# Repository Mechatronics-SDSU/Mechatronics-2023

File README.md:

# SDSU Mechatronics 2023

# About contributions

If you are unsure where to start, ask Software Project Manager or Software Lead.

Build and environment setup instructions are located in the docs. Refer to them before running `git clone` on this repository!

# About this repo

This repository has required code styling and commit rules. See style guide below for details.

ONLY upload source code. Do NOT commit binaries or Docker containers to this repository.

Pull request to master requirements:
Approved PR in `yourfeaturename-beta` branch from ANY project manager or the software lead is *required*. See below for details.

To begin development on a new feature, it is *recommended* to create a new branch from the `beta` branch, not the `master` branch, naming it `yourfeaturename_yourfulltable-dev`. When code is ready for submission, code is *required* be merged to a `yourfeaturename-beta` branch where a PR is then submitted, along with linking relevant issues here on GitHub. ***If you do NOT name your branch with the*** `-beta` ***naming convention, it is assumed the code is not ready to be merged and as a result will not be merged***.

Contributions are tracked via Git and GitHub but it is still *recommended* to comment your name and date on files worked on.

[Python installation and setup guide](src/man/python_setup_guide.md)

Python styling guide: All code in Python must follow [our styling guide](src/man/styling_guide.md).

C/C++ styling guide: All C/C++ code must follow the [Linux Kernal styling guide](https://www.kernel.org/doc/html/v4.10/process/coding-style.html).

Git naming conventions and usage: To make your own branches and push to this repository, read [our Git Guide](src/man/git_guide.md).

# About Scion

### Scion is the SDSU Mechatronics robot for the 2022 RoboSub Competition.

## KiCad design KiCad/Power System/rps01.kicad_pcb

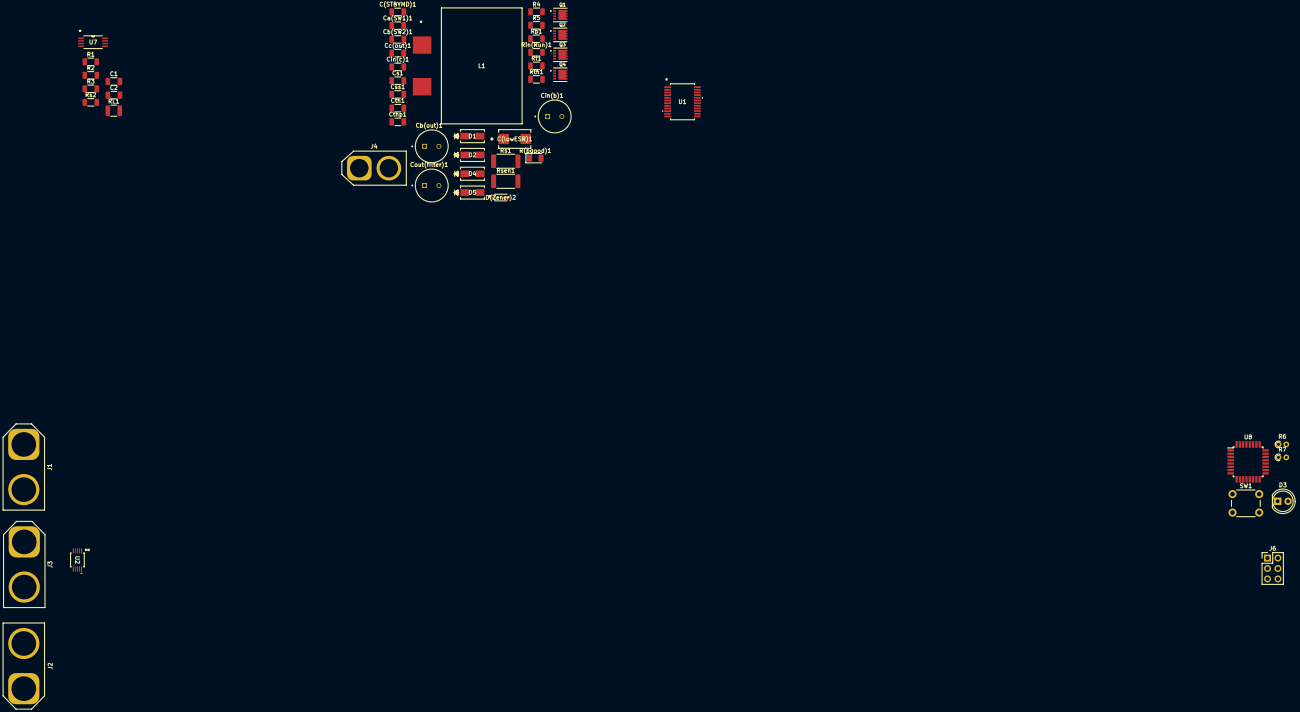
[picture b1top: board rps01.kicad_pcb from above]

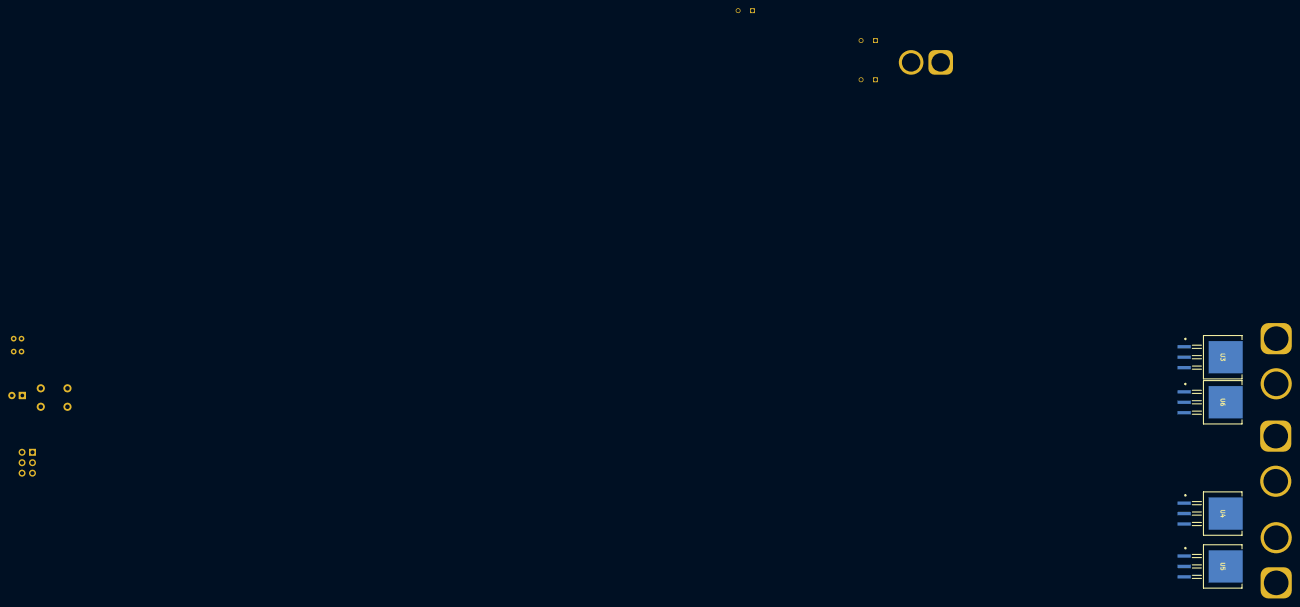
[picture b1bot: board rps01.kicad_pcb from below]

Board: 2 copper layers, 56 parts (4 on the bottom side), 38 nets, no tracks yet.

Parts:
C1, C2: 0.1mu; C_1206_3216Metric
C(STBYMD)1: 0.001u; C_1206_3216Metric
C(lowESR)1: 4.7u; LOWESRCAPMP7.6X4.3_3.1N_KEM
Ca(SW1)1: 0.22u; C_1206_3216Metric
Cb(SW2)1: 0.22u; C_1206_3216Metric
Cb(out)1: 330u; LargeCAPSCAPPRD350W60D800H1200
Cc(out)1: 47u; C_1206_3216Metric
Cin(b)1: 270u; LargeCAPSCAPPRD350W60D800H1200
Cin(c)1: 10u; C_1206_3216Metric
Cout(filter)1: 330u; LargeCAPSCAPPRD350W60D800H1200
Cs1: 100p; C_1206_3216Metric
Css1: 0.001u; C_1206_3216Metric
Cth1: 10000p; C_1206_3216Metric
Cthp1: 47p; C_1206_3216Metric
D1, D2, D4, D5: D_Schottky; CR_SMA_320-340AE_DIO
D3: LED; LED_D5.0mm
D(Zener)2: D_Zener; SOD123_DIO
J1: XT90 BAT1; AMASS_XT90-F_1x02_P11.00mm_Vertical
J2: XT90 BAT2; AMASS_XT90-F_1x02_P11.00mm_Vertical
J3: XT90 ESC Output; AMASS_XT90-M_1x02_P11.00mm_Vertical
J4: XT30PW Horizontal; AMASS_XT60-F_1x02_P7.20mm_Vertical
J6: 6pin; PinHeader_2x03_P2.54mm_Vertical
L1: 6.8u; IND_410680_WRE
Q1, Q2, Q3, Q4: NMOS; Q1Q2TRANS_FDMC86520L
R1: 4.7k; R_1206_3216Metric
R2: 10k; R_1206_3216Metric
R3: 1k; R_1206_3216Metric
R4, R5: 100; R_1206_3216Metric
R6: 10K; R_Axial_DIN0204_L3.6mm_D1.6mm_P1.90mm_Vertical
R7: 1k; R_Axial_DIN0204_L3.6mm_D1.6mm_P1.90mm_Vertical
R(pgood)1: 100k; LED_1206_3216Metric
RL1: 72.3k; R_1210_3225Metric
Rb1: 4.3K; R_1206_3216Metric
Rin(Run)1: 51K; R_1206_3216Metric
Rs1: 6m; R_2512_6332Metric
Rs2: 0.5m; R_1206_3216Metric
Rsen1: 6m; R_2512_6332Metric
Rt1: 100K; R_1206_3216Metric
Rth1: 124K; R_1206_3216Metric
SW1: SW_Push_Open; SW_PUSH_6mm
U1: LTC3780EG-TRPBF; SSOP-24_G_LIT
U2: LTC4416EMS-1-TRPBF; MSOP-10_MS_LIT
U3, U4, U5, U6: NP100P04PLG-E1-AY; PRSS0004AL-A_REN
U7: INA139NA/250; PW8
U8: ATmega328PB-A; TQFP-32_7x7mm_P0.8mm

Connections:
+5V: J6.5, R6.2, U8.4 (VCC)
/19V Boost/Vout: Cb(out)1.1, Cc(out)1.1, Cout(filter)1.1, D1.1 (K), J4.1, Q3.1 (D), Rt1.1
/Load Sharing/G1: U2.10 (G1), U3.1 (GATE), U6.1 (GATE)
/Load Sharing/G2: U2.6 (G2), U4.1 (GATE), U5.1 (GATE)
/Load Sharing/V1: J1.2, U2.2 (E1), U2.9 (V1), U3.2 (DRAIN), U3.4 (FIN), U6.2 (DRAIN), U6.4 (FIN)
/Load Sharing/V2: J2.2, U2.7 (V2), U4.2 (DRAIN), U4.4 (FIN), U5.2 (DRAIN), U5.4 (FIN)
/Load Sharing/VS: Cin(b)1.1, Cin(c)1.1, J3.1, Q1.1 (D), Rin(Run)1.1, U1.21 (VIN), U2.8 (VS), U3.3 (SOURCE), U4.3 (SOURCE), U5.3 (SOURCE), U6.3 (SOURCE)
GND: C1.2, C2.1, C(STBYMD)1.2, C(lowESR)1.2, Cb(out)1.2, Cc(out)1.2, Cin(b)1.2, Cin(c)1.2, Cout(filter)1.2, Css1.1, Cth1.2, Cthp1.2, D(Zener)2.2 (A), J1.1, J2.1, J3.2, J4.2, J6.1, R3.2, R5.2, R7.2, RL1.2, Rb1.2, Rs1.2, Rsen1.2, SW1.1 (A), U1.7 (SGND), U1.9 (FCB), U1.10 (PLLFLTR), U1.17 (PGND), U1.20 (EXTVCC), U2.3 (GND), U2.4 (*E2), U7.2 (GND), U8.5 (GND), U8.21 (GND)
MISO: J6.6, U8.16 (PB4)
MOSI: J6.3, U8.15 (PB3)
unnamed: C1.1, R2.2, R3.1
unnamed: Cth1.1, Rth1.1
unnamed: Ca(SW1)1.2, D1.2 (A), L1.2, Q3.3 (S), Q4.1 (D), U1.22 (SW1)
unnamed: D2.2 (A), Q2.3 (S), Q4.3 (S), R4.1, Rs1.1, Rsen1.1
unnamed: Cb(SW2)1.1, D2.1 (K), L1.1, Q1.3 (S), Q2.1 (D), U1.15 (SW2)
unnamed: D3.2 (A), U8.13 (PB1)
unnamed: D3.1 (K), R7.1
unnamed: C(lowESR)1.1, D4.2 (A), D5.2 (A), R(pgood)1.1, U1.19 (INTVCC)
unnamed: Ca(SW1)1.1, D4.1 (K), U1.24 (BOOST1)
unnamed: Cb(SW2)1.2, D5.1 (K), U1.13 (BOOST2)
unnamed: D(Zener)2.1 (K), Rin(Run)1.2, U1.8 (RUN)
unnamed: J6.2, R6.1, SW1.2 (B), U8.29 (~RESET/PC6)
unnamed: Q1.2 (G), U1.14 (TG2)
unnamed: Q2.2 (G), U1.16 (BG2)
unnamed: Q3.2 (G), U1.23 (TG1)
unnamed: Q4.2 (G), U1.18 (BG1)
unnamed: R1.2, R2.1
unnamed: Cthp1.1, Rth1.2, U1.5 (ITH)
unnamed: R(pgood)1.2, U1.1 (PGOOD)
unnamed: Cs1.2, R4.2, U1.3 (SENSE+)
unnamed: Cs1.1, R5.1, U1.4 (SENSE-)
unnamed: Css1.2, U1.2 (SS)
unnamed: C(STBYMD)1.1, U1.12 (STBYMD)
unnamed: Rb1.1, Rt1.2, U1.6 (VOSENSE)
unnamed: C2.2, RL1.1, U7.1 (OUT)
unnamed: R1.1, Rs2.1, U7.3 (VIN+), U7.5 (V+)
unnamed: Rs2.2, U7.4 (VIN-)
SCK: J6.4, U8.17 (PB5)

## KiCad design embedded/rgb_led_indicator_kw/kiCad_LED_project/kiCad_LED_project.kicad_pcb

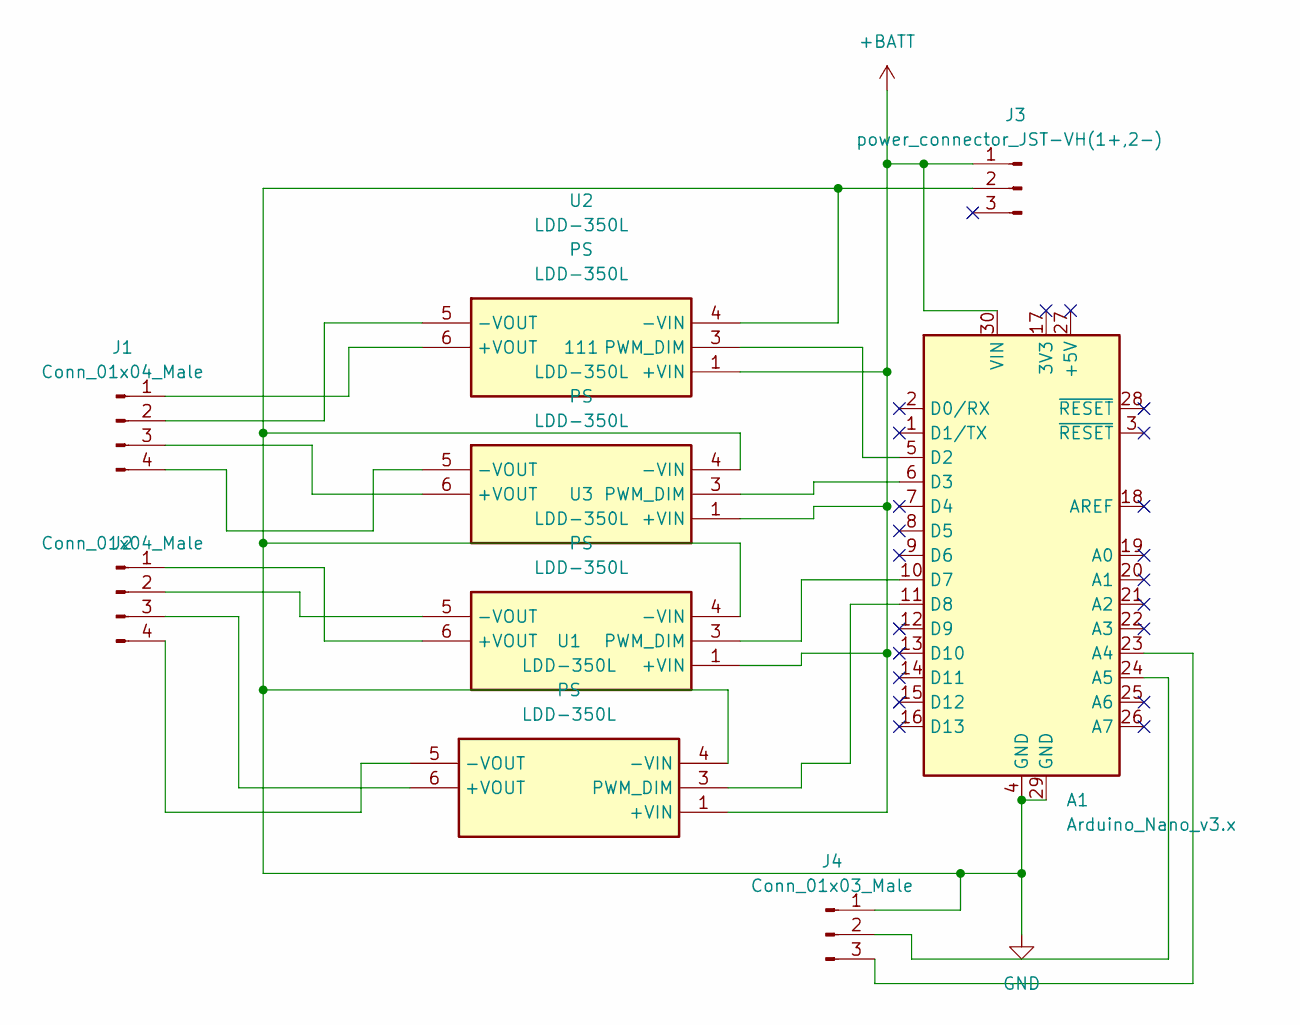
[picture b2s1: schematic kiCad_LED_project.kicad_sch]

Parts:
111: LDD-350L; LDD350L; Manufacturer_Part_Number LDD-350L; Mouser Part Number 709-LDD-350L
A1: Arduino_Nano_v3.x; Arduino_Nano
J1, J2: Conn_01x04_Male; JST_XH_B4B-XH-AM_1x04_P2.50mm_Vertical
J3: power_connector_JST-VH(1+,2-); JST_VH_B3P-VH-FB-B_1x03_P3.96mm_Vertical
J4: Conn_01x03_Male; JST_PH_B3B-PH-K_1x03_P2.00mm_Vertical
U1, U2, U3: LDD-350L; LDD350L; Manufacturer_Part_Number LDD-350L; Mouser Part Number 709-LDD-350L

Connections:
+BATT: 111.1 (+VIN), A1.30 (VIN), J3.1, U1.1 (+VIN), U2.1 (+VIN), U3.1 (+VIN)
GND: 111.4 (-VIN), A1.4 (GND), A1.29 (GND), J3.2, J4.1, U1.4 (-VIN), U2.4 (-VIN), U3.4 (-VIN)
unnamed: A1.5 (D2), U2.3 (PWM_DIM)
unnamed: 111.3 (PWM_DIM), A1.6 (D3)
unnamed: A1.10 (D7), U3.3 (PWM_DIM)
unnamed: A1.11 (D8), U1.3 (PWM_DIM)
unnamed: A1.23 (A4), J4.3
unnamed: A1.24 (A5), J4.2
unnamed: J1.1, U2.6 (+VOUT)
unnamed: J1.2, U2.5 (-VOUT)
unnamed: 111.6 (+VOUT), J1.3
unnamed: 111.5 (-VOUT), J1.4
unnamed: J2.1, U3.6 (+VOUT)
unnamed: J2.2, U3.5 (-VOUT)
unnamed: J2.3, U1.6 (+VOUT)
unnamed: J2.4, U1.5 (-VOUT)

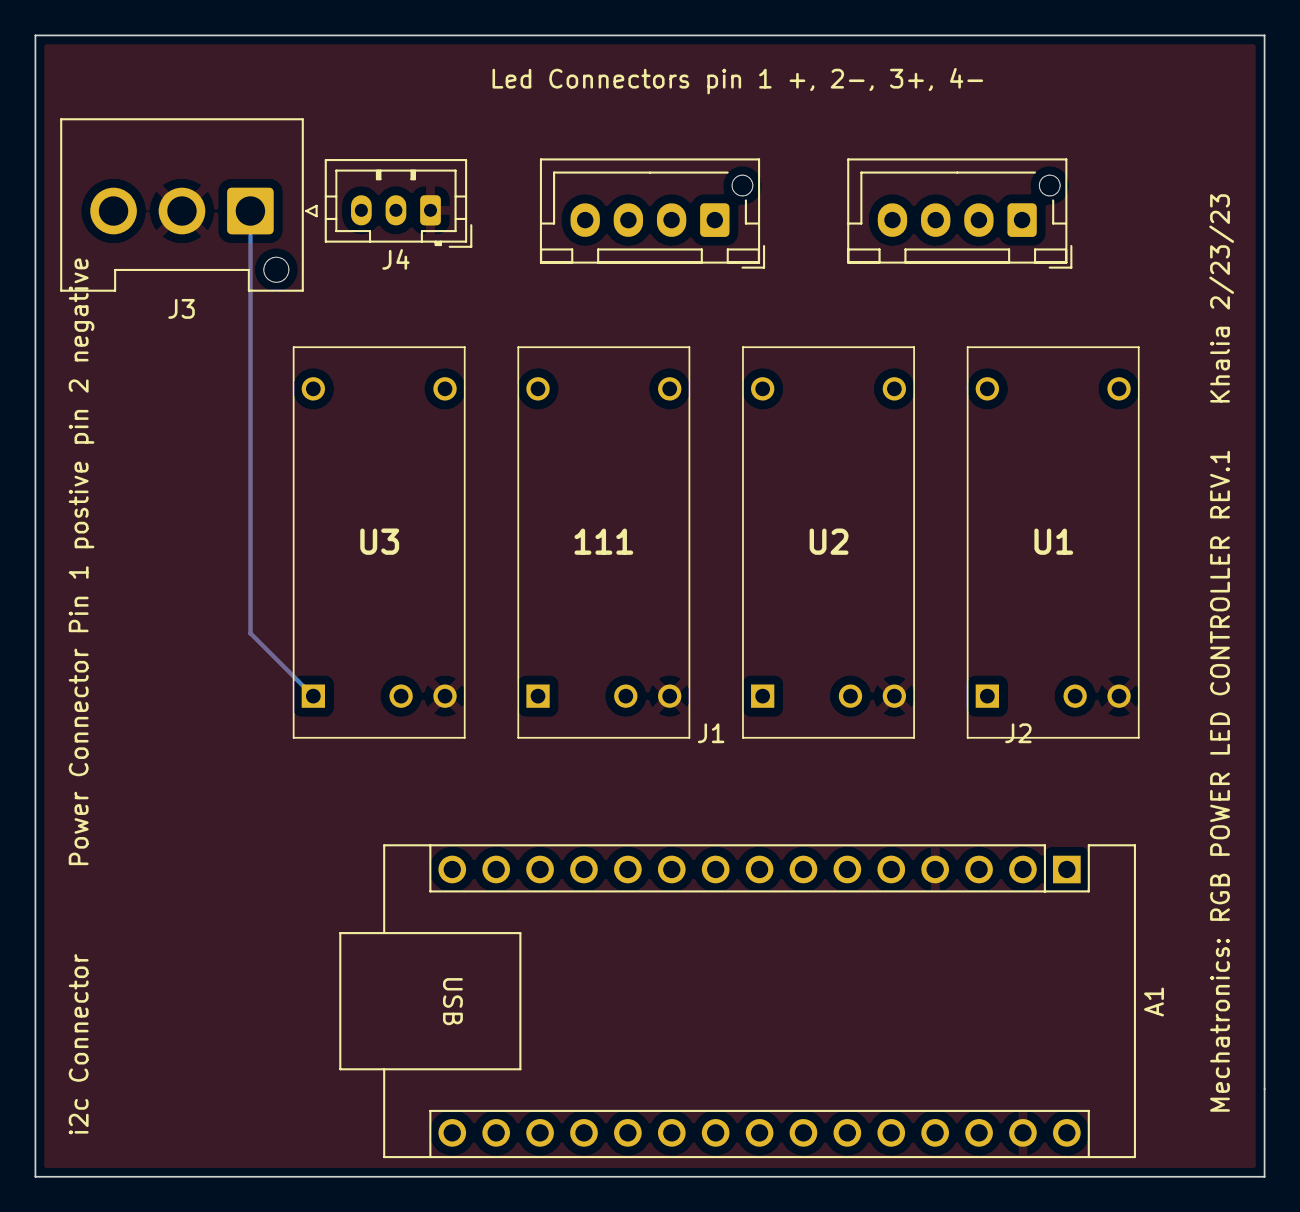
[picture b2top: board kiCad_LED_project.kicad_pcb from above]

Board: 2 copper layers, 71.1 x 66.0 mm, 9 parts (0 on the bottom side), 16 nets.

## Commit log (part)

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2023-03-04 updated distance_detector.py
    Made it so it keeps running after outputting "stop".
2023-03-04 Added V0x8 PCB KiCad library footprints and symbols
2023-03-04 Added readme for PCB footprints install
2023-03-04 Update distance_detector.py
    Updated header
2023-03-06 Updated T4 dependencies documentation
2023-03-07 G changed zed msgs
2023-03-07 Added HARD_KILL relay control, fixed EMBSYS STOW logic
2023-03-07 Moved sensor initialization to messaging instead of on by default
2023-03-07 Updated pinout for potential PING sonar in future
2023-03-08 Updated readme dependencies description
2023-03-12 Applying Correct Gitignore To Clean Up - Zix
2023-03-12 Add Controller Node Documentation
2023-03-12 Changed From Relative to Absolute Imports
2023-03-12 Add Vision Documentation and Cleanup -Zix
2023-03-12 Junebug Commit
2023-03-12 Plotting of Depth Map
2023-03-12 Brain node template filled out
2023-03-14 Deleting yolov5m.pt To Clear Up Github
2023-03-16 added UnifiedCanDriver
2023-03-17 Debugging on orin; cstring error in unified_can_driver.cpp
2023-03-23 Implementing Junebug PIDs
2023-03-23 Commiting Files Not Automatically Added
2023-03-23 Junebug PID Code
2023-03-23 Tested driver in VM; added documentation
2023-03-23 Brain Node Code Added For Turn Sequence - Zix
2023-03-23 New Scripts for Junebug
2023-03-24 Brain Node Half Functionality
2023-03-24 Brain Node Function Pointers Work
2023-03-24 Extended documentation
2023-03-24 Tuned PIDs and Tuned Brain Node Algorithm - Zix
2023-03-24 Changes To Control Nodes For Testing - Zix
2023-03-24 Created Zed Orientation Node - Zix
2023-03-24 Make Git Happy With Dumb Conflict Resolution- Zix
2023-03-25 Fixed My PID Code Trash Coding Practices - Zix
2023-04-02 Saving Before Rehaul To ROS Workspace for Control System
2023-04-03 Revamping Control System, Complete with State Node
2023-04-03 Added Trig w/ Zed Position XY for Relative - Zix
2023-04-03 Changes to Launch Configuration
2023-04-03 Changes After Testing
2023-04-03 Fixed Arctan For Angle Wrap - Zix
2023-04-03 Update Loop Condition For Valid State - Zix
2023-04-03 Changes to Controller System After Testing - Zix
2023-04-03 Ignore Position Parameter Testing
2023-04-04 Quantum Theory Duality Debugging And Scripts
2023-04-04 relative hackery for testing - Zix
2023-04-05 Zed Vision Node Stop idea - Zix
2023-04-05 Remove Negative Manipulation in Relative State - Zix
2023-04-05 typedef gang - Zix
2023-04-05 Fix build issues with new types
2023-04-06 Zed Vision Integrated With Position - Zix
2023-04-06 Robot Can Accept new Command After Blockage
2023-04-13 Cleaned up code in PID/Mediator - Zix
2023-04-14 Going back to yolov5 implementation, will check in the club tomorow morning if correct
2023-04-26 Added Kicad
    Kicad rgb pcb
2023-05-12 CAD files
2023-05-20 fixed axes values; controller is pool test read
2023-05-20 New Tmux Scripts (yay) - Zix
2023-05-20 Porting Junebug Controls to Sub
2023-05-20 Vision Script Ready For Pool Testing
2023-05-21 fixed label data output
2023-05-21 Startup Scripts Revamp for Pool Testing
2023-05-21 startup script further improved with motor tests
2023-05-21 Script checks if CAN is Enabled
2023-05-21 startup script draft complete - Zix
2023-05-21 New Build Script For ROS Packages - Zix
2023-05-21 Small Changes For PoolTest Doc
2023-05-22 Temporarily Uploading test_node i need for smthng
2023-05-24 PID Port Start - Zix
2023-05-25 Porting Control System Continued
2023-05-25 Porting Control System Continued - Zix
2023-05-25 Stabilize Sub Code Added - Zix
2023-05-25 Fixed Update Controller Bug - Zix
2023-05-25 Small Controller Changes After Testing - Zix
2023-05-27 Controller Values Changed I don't know why - Zix
2023-05-29 new_make_dataset.py
2023-05-29 Fix Vision Script
2023-05-29 Fix CAN Enable in Unified Driver - Zix
2023-05-29 Build Script Remove Ignores - Zix
2023-05-29 Controller Reference Fix - Zix
2023-05-29 Controller Uses Correct CAN Request - Zix
2023-05-29 Small change for build script - Zix
2023-06-01 Disable Broken Module Load (iPnger 12) -Zix
2023-06-01 Controller Sends Safety Mode Frame - Zix
2023-06-01 Robot thrust mapper pass in as ROS parameter - Zix
2023-06-01 Revise PID to use condense control interface - Zix
2023-06-03 Power Adjustment to Controller - Zix
2023-06-03 Edit to Motor CAN ID - Zix
2023-06-03 Stabilization Service Implemented - Zix
2023-06-03 Convenience dummy data script - Zix
2023-06-03 Convenient commands to put in /usr/local/bin - Zix
2023-06-03 I forgot one - Zix
2023-06-03 Added Messages to Convenience Script - Zix
2023-06-03 State Node Now Properly Uses ROS Params - Zix
2023-06-03 Made launch and current_state_node prettier - Zix
2023-06-03 I forgot to add the namespace cuz i suck - Zix
2023-06-03 Clear variable names for current_state - Zix
2023-06-03 Tmux adds candump
2023-06-04 State node uses all axes for control porting - Zix
2023-06-04 Updated pid params for next pool test - Zix
2023-06-04 fixed UCD DVL data issues
2023-06-06 Commit Pool Test Changes
2023-06-07 DVL Node Skeleton
2023-06-08 Filled Out Control Interface - Zix
2023-06-08 Fix Weird Git Glitch
2023-06-08 Mediator Node Given All Translation Methods - Zix
2023-06-08 pid_params adjusted before pool test - Zix
2023-06-08 Fixing Errors in Pid Node
2023-06-08 PID New Methods Corrected - Zix
2023-06-09 overdue control cleanup - Zix
2023-06-09 Correct Headers to Match Functions - Zix
2023-06-09 Built PID and Mediator New System - Zix
2023-06-09 Fix current state node really quick - Zix
2023-06-10 Fixed That Seg Fault Issue - Zix
2023-06-10 Adding extra field to pid class - Zix
2023-06-10 Special Updates - Zix
2023-06-10 Final Changes - Zix
2023-06-10 Testing Updates - Zix
2023-06-10 Better pid params - Zix
2023-06-10 Think i fix controller and it sucked booty - Zix
2023-06-11 Fixed WAYFDVL ID bug, good catch Connor
2023-06-13 pool test ready -HectorA.
2023-06-14 Unit Test Directory - Zix
2023-06-15 ISR safe version of ESC Signal Kill on Soft/Hard Kill
2023-06-15 Tested and verified ISR safe cycle counter based delays
2023-06-16 Validates ESC reset on kill, 0.5s timeout. DREQ error checking and 024# messaging added and tested
2023-06-17 Fix Inverted Pitch PID
2023-06-17 Activate Orientation Callback For Pool Test - Zix
2023-06-17 I changed the imports for AHRS and zed_vision to absolute again because they were making me mad, also python is a garbage language for the record
2023-06-19 Dynamic Motor Count for Controller - Zix
2023-06-21 Dry Test Passed - Zix
2023-06-21 AHRS in Launch, Dont Anything You Scoundrels - Zix
2023-06-30 Add Rough Draft of A50 node - Zix
2023-07-01 Rewrote a50 in C++ because i dont condone trash languages
2023-07-01 Added some comments to explain but bet 50$ no one reads it - Zix
2023-07-01 Add Reset Command On Start of A50 Node - Zix
2023-07-01 Whoops i forgot a semicolon - Zix
2023-07-01 Got rid of some unnecessary things - Zix
2023-07-02 Lost 5 Years of Life getting GUI Node to Build - Zix
2023-07-02 Lost 3 More Years Getting Ros Thread and QT Thread Running at Same Time + Stylesheet
2023-07-02 Add Kp Ki Kd Dials to GUI - Zix
2023-07-02 underwater gate vision
2023-07-03 G fixing scale_segments method
2023-07-03 G chaning coordinate system to be compatible with ROS. X is now forward. Y is now Left. Z is UP. Origin is left camera in zed
2023-07-04 Fix Horse, Change Precision to One Decimal - Zix
2023-07-04 Remove Python A50 - Zix
2023-07-04 Add New Nodes to Launch - Zix
2023-07-05 Brain Work In Progress For Gate - Zix
2023-07-05 Update /usr/local/bin scripts - Zix
2023-07-05 Async Gate Worked - Zix
2023-07-05 Made async function dynamic
2023-07-05 Clean Up Brain - Zix
2023-07-05 Added Movements To Brain - Zix
2023-07-06 Brain Node Cleanup - Zix
2023-07-06 Go Through Gate Changes - Zix
2023-07-07 Tied Controller Buttons To CAN Commands - Zix
2023-07-07 PID Activate Service
2023-07-08 Make Command Timeout Less Sensitive - Zix
2023-07-08 Add Light Off to Controller
2023-07-08 Add 2D bounding box to scion_types manually - Zix
2023-07-08 In progress changes for gate centering - Zix
2023-07-08 Quickly add equal logic for two pixel points - Zix
2023-07-10 Remove brackets I accidentally put in JSON - Zix
2023-07-10 Let mediator accept stop command w/o turn - Zix
2023-07-10 Take prints out of Brain node - Zix
2023-07-10 Improve readability of brain node - Zix
2023-07-10 Add Pid Tuning message to Gui
2023-07-10 Auto button works, BRESC transition in main
2023-07-11 Cleaned up mediator/pid action server - Zix
2023-07-11 Clean up white spacing PID Node - Zix
2023-07-11 More Cleanup, Comment Out Stop From Camera - Zix
2023-07-11 Fix tuning Scale factor GUI / PID - Zix
2023-07-11 PID param change for tomorrow - Zix
2023-07-12 Decrease PID Command Completion Sensitivity - Zix
2023-07-12 Matrix inverted for motor changes - Zix
2023-07-12 Enable and mode set moved to init - Zix
2023-07-12 PID params - Zix
2023-07-14 Changes that should help with control stability
2023-07-15 Change zed vision bounding box from 3d to 2d - Zix
2023-07-16 fix ful dir for vision josh
2023-07-17 Add Modifier for Vision Scripts
2023-07-18 Add filtering to vision data - Joseph/Zix
2023-07-19 Accidentally Ignored CMakeLists.txt - Zix
2023-07-19 unified_can_driver: Implemented sub state decoder; New ROS2 topic submarine_state; new scion_types msg
2023-07-19 Center Robot Function Implemented - Zix
2023-07-19 Change Mediator Back to Not Test Mode - Zix
2023-07-19 Fix Keypoint Msg - Zix
2023-07-19 Fix Hanging Thread in Centering - Zix
2023-07-19 vision yaml & pt placeholder dev-josh
2023-07-20 Cleaning Things Up For Pool Test Tomorrow- Zix
2023-07-20 More cleaning - Zix
2023-07-20 Allow For Easy Disabling of PID Axes - Zix
2023-07-20 Clean PID - Zix
2023-07-20 Update zed_vision.py both yamls dev-josh
2023-07-20 Update zed_vision.py both weights dev-josh
2023-07-20 Allow brain to track object identifier - Zix
2023-07-20 Update zed_vision.py pt to default dir dev-josh
2023-07-23 Actually Adding Some Unit Tests to This Codebase for Once - Zix
2023-07-23 Make Vision Files Easier To Change - Zix
2023-07-23 Add Populate Filter Buffer Test For Brain - Zix
2023-07-24 Address Brain Node Bugs + Add Unit Tests - Zix
2023-07-24 Update make_dataset.py new parent dir dev-josh
2023-07-24 Update make_dataset.py dev-josh
2023-07-26 Refactor in Progress - Dependencies Linked, 1st gtest Created - Zix
2023-07-27 Add Google Test to External Fetch - Zix
2023-07-27 New Storage Repository Called File - Storage - Zix
2023-07-27 Storage Files Moved to New Repo - Zix
2023-07-27 Storage Files Moved to New Repo
2023-07-27 Remove unused Class - Zix
2023-07-27 Remove Unused Directory
    Download github slow as hell
2023-07-27 Make CMake Directory More Dynamic - Zix
2023-07-27 Remove DVL Node - Zix
2023-07-27 Add in Node Library and Test Library - Zix
2023-07-27 Finish Refactor Part 1 (Headers Plus Test Framework Set Up - Zix)
2023-07-28 Accidentally deleted hashtag, compiler gave me 8000 line error - Zix
2023-07-28 Adding Integration Tests
2023-07-28 Brain tests converted to googletest
2023-07-28 Add Pid Slew Rate Test
2023-07-29 Wait For Connors Message + Fix No vision - Zix
2023-07-29 Aysnc Tests - Zix
2023-07-29 Fixed The Filter Thing Again I Hate Programming
2023-07-30 Slew Condition Adjust
2023-07-31 Fix launcher_node config naming
2023-07-31 Added Necessary Garbage Python Boilerplate - Zix
2023-07-31 Add light to listen launch - Zix
2023-08-02 Hail Mary Attempt to make button work - Zix
2023-08-02 Vision Changes to Match Percy
2023-08-02 Control map for comp
2023-08-02 Alter wait logic
2023-08-02 launch change
2023-08-03 New pynput node -zix
2023-08-07 Made new GUI - Halie
2023-08-07 Add DockerFile - Zix
2023-08-07 new stuff for gui
2023-08-07 Update Dockerfile - Zix
2023-08-08 added text box to display published pid msg data
2023-08-08 can use up/down arrow key to move between lineedit
2023-08-09 debug test_gui node
2023-08-09 Create PID_graph.py
    This (should, not yet) plots current and desired position of the PIDS, it also (should, not yet) plots the power of motors
2023-08-11 Allow selection of nodes to generate JSON
2023-08-11 Remove merge strings - Zix
2023-08-11 publish json string onto ros topic gui_data
2023-08-13 meow <3
